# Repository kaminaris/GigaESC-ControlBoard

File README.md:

# GigaControl

Compact six-layer control card for modular GigaESC motor controllers. The MCU, CAN transceiver, IMU and signal conditioning live here; the MOSFET power stage and power supply are separate boards.

## Board views

## Hardware

- STM32F405RGT6 with an 8 MHz oscillator.
- SIT3051 CAN transceiver with onboard 120 Ω termination.
- LSM6DS3TR-C IMU on I²C.
- REF3033 analog supply/reference, also exported to the power board.
- Three 1 mm pitch 2×10 female sockets for power, PWM, feedback and external interfaces.
- USB data, SWD, Hall inputs, motor temperature, SERVO, UART and shared SPI/ADC signals pass through the power board.

Open `GigaControl.kicad_pro` in KiCad 10. Local symbols and footprints are included. Keep `HDR-TH_20P-P1.00-V-F-R2-C10-S1.00.step` beside the project for the connector models. Some other models still use `KICAD9_3DMODEL_DIR`; configure that variable if they are missing in KiCad 10.

See [connector pinout](CONNECTOR_PINOUT.md) for the current interface and [firmware adaptation guide](bldc-config/VESC-CONFIG-GUIDE.md) for the supplied VESC configuration template.

## Design notes

- 1 µF VCAP capacitors, the shared SPI/ADC filtering and the REF3033 arrangement are intentional choices reported tested by the designer. This does not imply validation of every optional interface mode.
- Bridge JP1 only when U3 (REF3033) is not fitted; it supplies VDDA from the main 3.3 V rail.
- Phase numbering is local to each board. The current GigaDFN56 pairing exchanges phase groups 1 and 3 consistently across PWM and feedback; phase 2 is unchanged.
- Adapt the firmware configuration to the actual power board and application before use.

## Repository housekeeping

Keep the KiCad project, active schematic sheets (`MCU`, `Filters`, `CAN`, `IMU`), local libraries, library tables, connector STEP model and firmware configuration sources.

Cleanup candidates, not deleted:

- Regenerable/local files: `fp-info-cache`, `GigaControl.dsn`, `GigaControl.step`, `.idea/`, `*.kicad_prl`, and `_autosave-*`.
- Old recovery files: `X3.0CH-Library.bak` and `GigaControl-backups/`, once their contents are no longer needed. Leave active lock files alone while KiCad is open.
- Unreferenced schematic files: `Connectors.kicad_sch`, `ESP32.kicad_sch`, and the empty `Power.kicad_sch`. Archive or remove after confirming they are not wanted as design references.
- Legacy footprints: `X3.0CH-Master`, `X3.0CH`, and `SolderJumper-3-0.5-Small` are not used by the current board; retain if other projects share this library.
- `production/` contains generated outputs; preserve any release/manufacturing records that still matter.

Review on 2026-09-22: saved-board DRC reports no violations, unconnected items or schematic mismatches. ERC has one warning for PB2 tied to GND. These checks do not replace hardware validation.

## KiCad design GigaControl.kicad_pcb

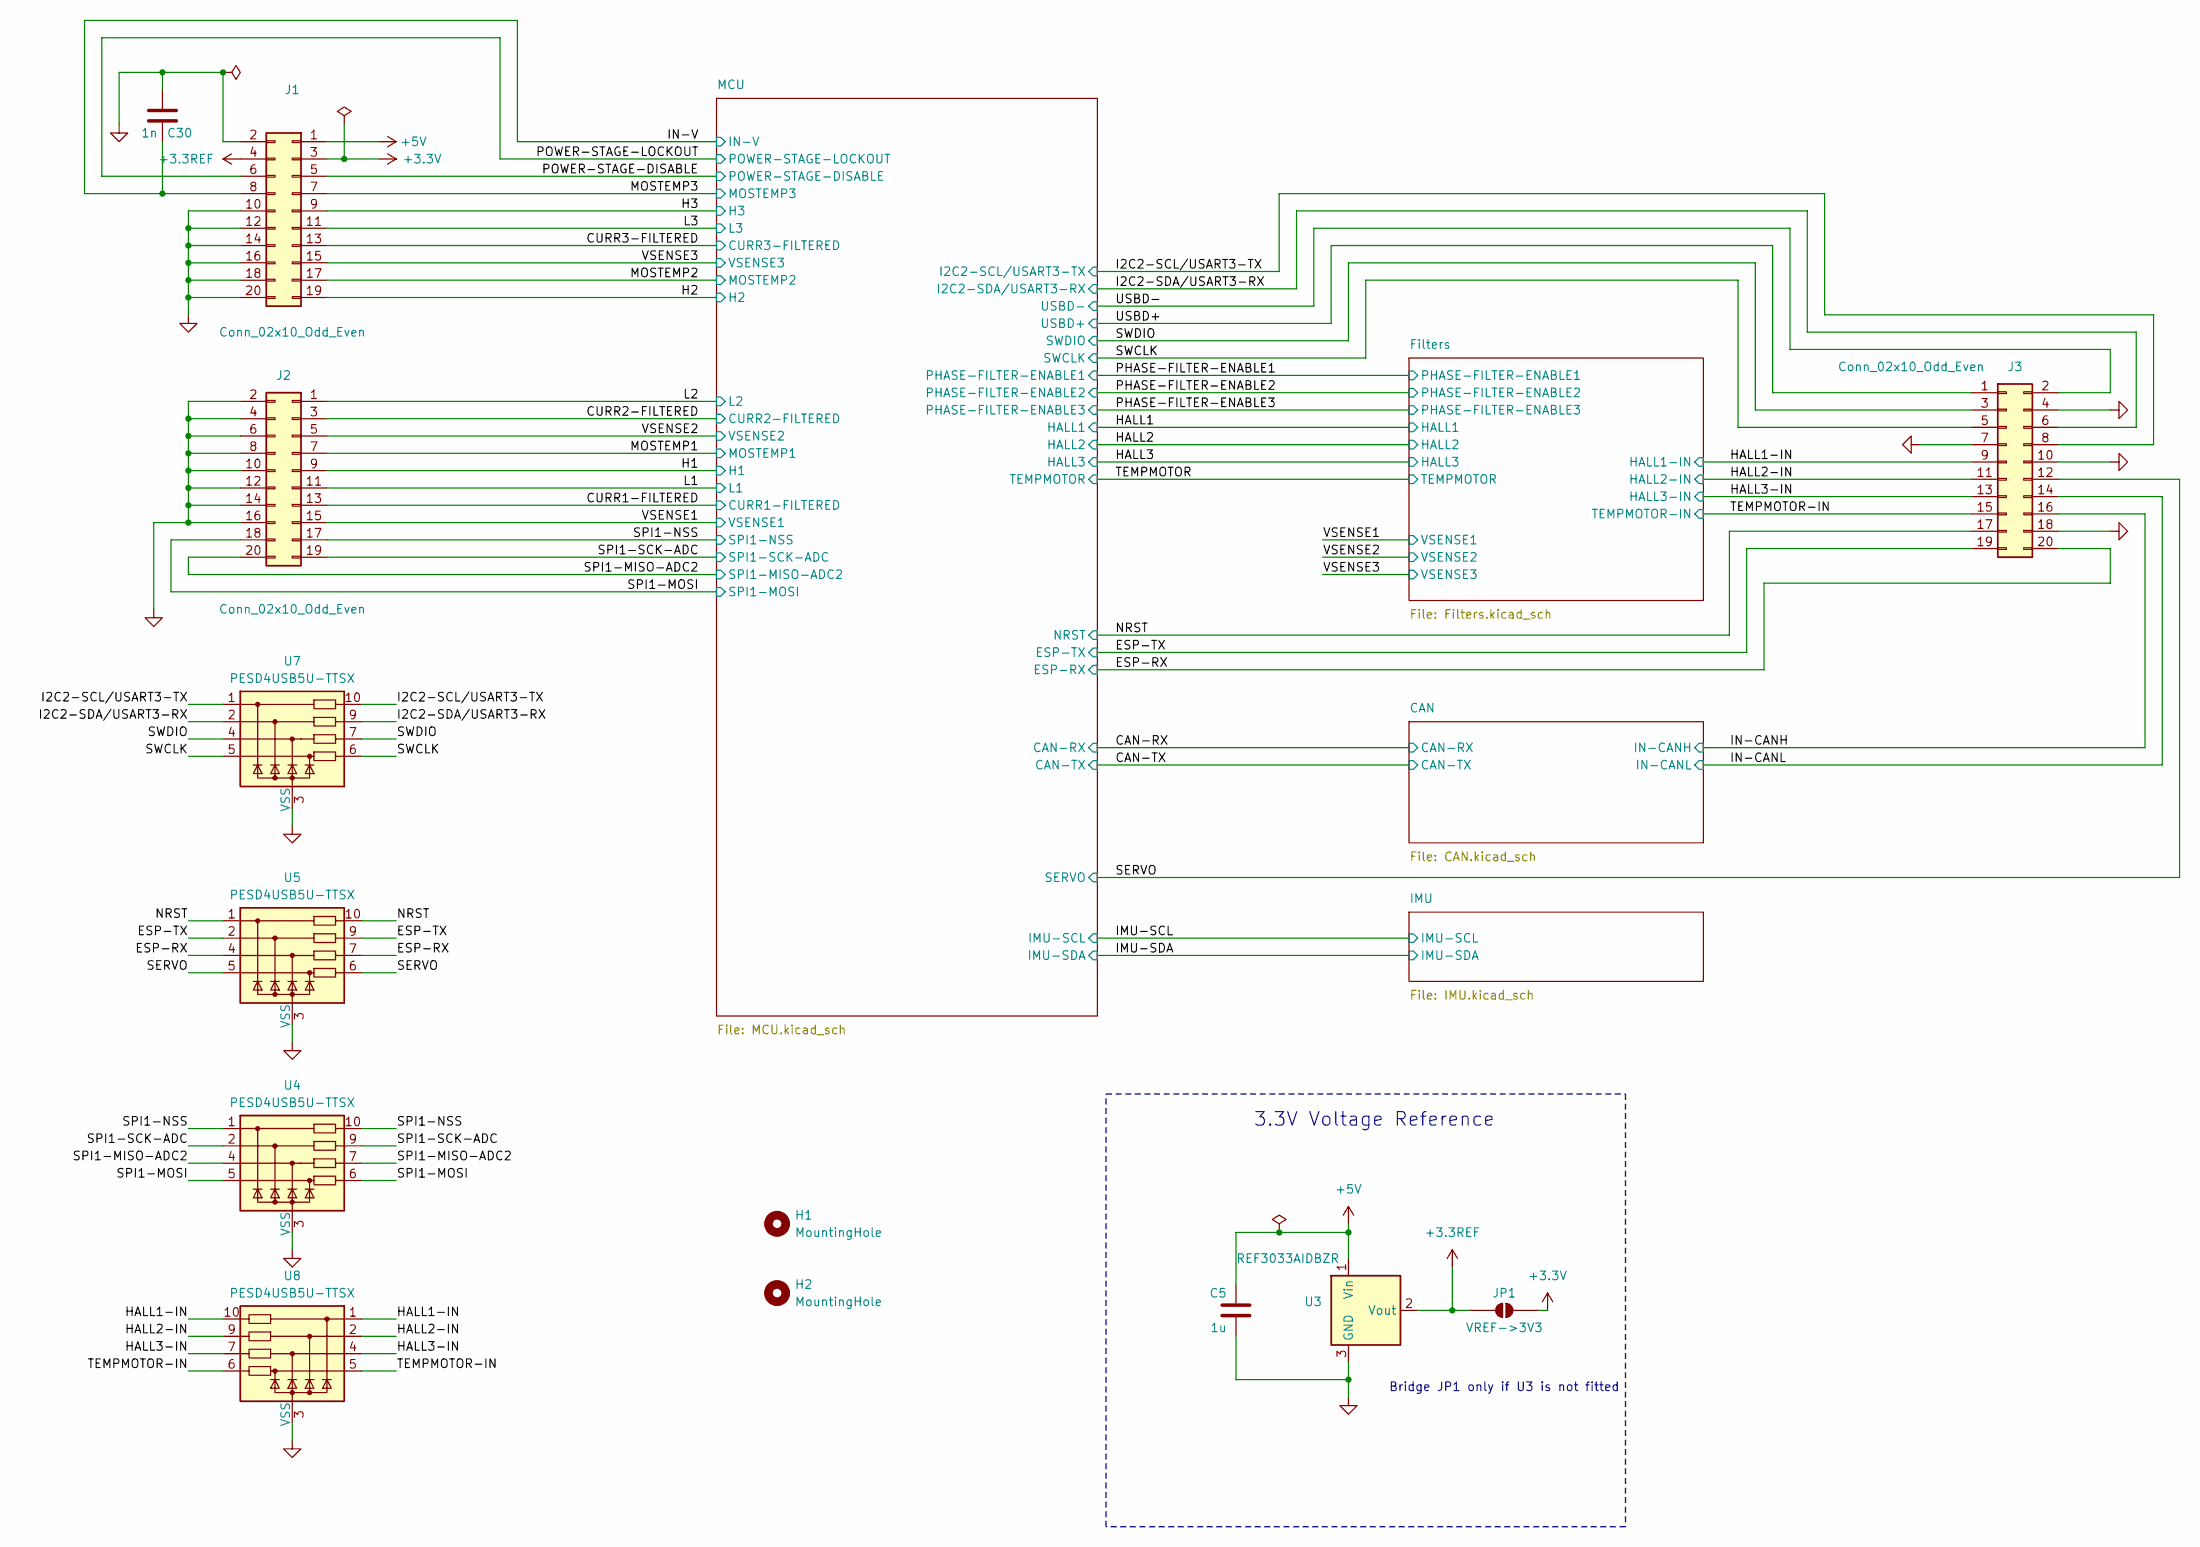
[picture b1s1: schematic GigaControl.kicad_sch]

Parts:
C5: 1u; C_0402_1005Metric; MPN C52923
C30: 1n; C_0402_1005Metric; MPN C1523
H1, H2: MountingHole; MountingHole_3.2mm_M3_DIN965
J1, J2, J3: Conn_02x10_Odd_Even; Hanxia_HX_PM1.0-2x10P_ZC; MPN HX PM1.0-2x10P ZC; LCSC C22465702
JP1: VREF->3V3; SolderJumper-2_P1.3mm_Open_RoundedPad1.0x1.5mm
U3: REF3033AIDBZR; SOT-23; MPN C36658; JLCRotOffset 0
U4, U5, U7, U8: PESD4USB5U-TTSX; Diodes_UDFN-10_1x2.5mm_P0.5mm

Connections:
+3.3REF: J1.4, JP1.1 (A), U3.2 (Vout); also elsewhere on the board
+3.3V: J1.3, JP1.2 (B); also elsewhere on the board
+5V: C5.1, J1.1, U3.1 (Vin)
/CURR1-FILTERED: J2.13; also elsewhere on the board
/CURR2-FILTERED: J2.3; also elsewhere on the board
/CURR3-FILTERED: J1.13; also elsewhere on the board
/ESP-RX: J3.20, U5.4, U5.7; also elsewhere on the board
/ESP-TX: J3.19, U5.2, U5.9; also elsewhere on the board
/H1: J2.9; also elsewhere on the board
/H2: J1.19; also elsewhere on the board
/H3: J1.9; also elsewhere on the board
/HALL1-IN: J3.9, U8.1, U8.10; also elsewhere on the board
/HALL2-IN: J3.11, U8.2, U8.9; also elsewhere on the board
/HALL3-IN: J3.13, U8.4, U8.7; also elsewhere on the board
/I2C2-SCL/USART3-TX: J3.8, U7.1, U7.10; also elsewhere on the board
/I2C2-SDA/USART3-RX: J3.6, U7.2, U7.9; also elsewhere on the board
/IN-CANH: J3.16; also elsewhere on the board
/IN-CANL: J3.14; also elsewhere on the board
/IN-V: C30.1, J1.8; also elsewhere on the board
/L1: J2.11; also elsewhere on the board
/L2: J2.1; also elsewhere on the board
/L3: J1.11; also elsewhere on the board
/MOSTEMP1: J2.7; also elsewhere on the board
/MOSTEMP2: J1.17; also elsewhere on the board
/MOSTEMP3: J1.7; also elsewhere on the board
/NRST: J3.17, U5.1, U5.10; also elsewhere on the board
/POWER-STAGE-DISABLE: J1.5; also elsewhere on the board
/POWER-STAGE-LOCKOUT: J1.6; also elsewhere on the board
/SERVO: J3.12, U5.5, U5.6; also elsewhere on the board
/SPI1-MISO-ADC2: J2.20, U4.4, U4.7; also elsewhere on the board
/SPI1-MOSI: J2.18, U4.5, U4.6; also elsewhere on the board
/SPI1-NSS: J2.17, U4.1, U4.10; also elsewhere on the board
/SPI1-SCK-ADC: J2.19, U4.2, U4.9; also elsewhere on the board
/SWCLK: J3.5, U7.5, U7.6; also elsewhere on the board
/SWDIO: J3.3, U7.4, U7.7; also elsewhere on the board
/TEMPMOTOR-IN: J3.15, U8.5, U8.6; also elsewhere on the board
/USBD+: J3.1; also elsewhere on the board
/USBD-: J3.2; also elsewhere on the board
/VSENSE1: J2.15; also elsewhere on the board
/VSENSE2: J2.5; also elsewhere on the board
/VSENSE3: J1.15; also elsewhere on the board
GND: C5.2, C30.2, J1.2, J1.10, J1.12, J1.14, J1.16, J1.18, J1.20, J2.2, J2.4, J2.6, J2.8, J2.10, J2.12, J2.14, J2.16, J3.4, J3.7, J3.10, J3.18, U3.3 (GND), U4.3 (VSS), U4.8 (VSS), U5.3 (VSS), U5.8 (VSS), U7.3 (VSS), U7.8 (VSS), U8.3 (VSS), U8.8 (VSS); also elsewhere on the board

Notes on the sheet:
3.3V Voltage Reference
Bridge JP1 only if U3 is not fitted

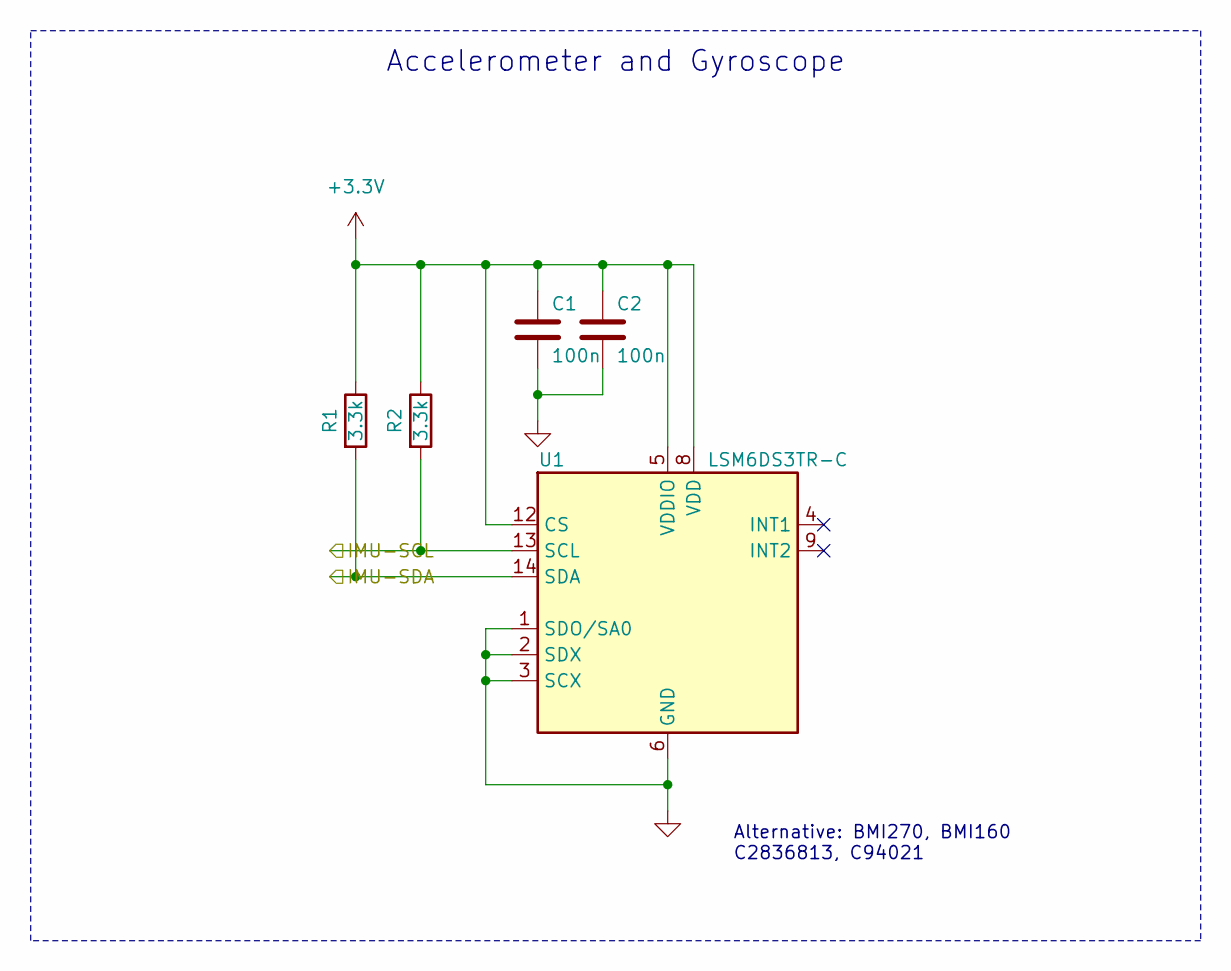
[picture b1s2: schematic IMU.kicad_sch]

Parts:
C1, C2: 100n; C_0402_1005Metric; MPN C1525
R1, R2: 3.3k; R_0402_1005Metric; MPN C25890
U1: LSM6DS3TR-C; LGA-14_3x2.5mm_P0.5mm; MPN C967633; JLCRotOffset -90

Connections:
+3.3V: C1.1, C2.1, R1.1, R2.1, U1.5 (VDDIO), U1.8 (VDD), U1.12 (CS); also elsewhere on the board
/IMU-SCL: R2.2, U1.13 (SCL); also elsewhere on the board
/IMU-SDA: R1.2, U1.14 (SDA); also elsewhere on the board
GND: C1.2, C2.2, U1.1 (SDO/SA0), U1.2 (SDX), U1.3 (SCX), U1.6 (GND), U1.7 (GND); also elsewhere on the board

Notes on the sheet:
Alternative: BMI270, BMI160 C2836813, C94021
Accelerometer and Gyroscope

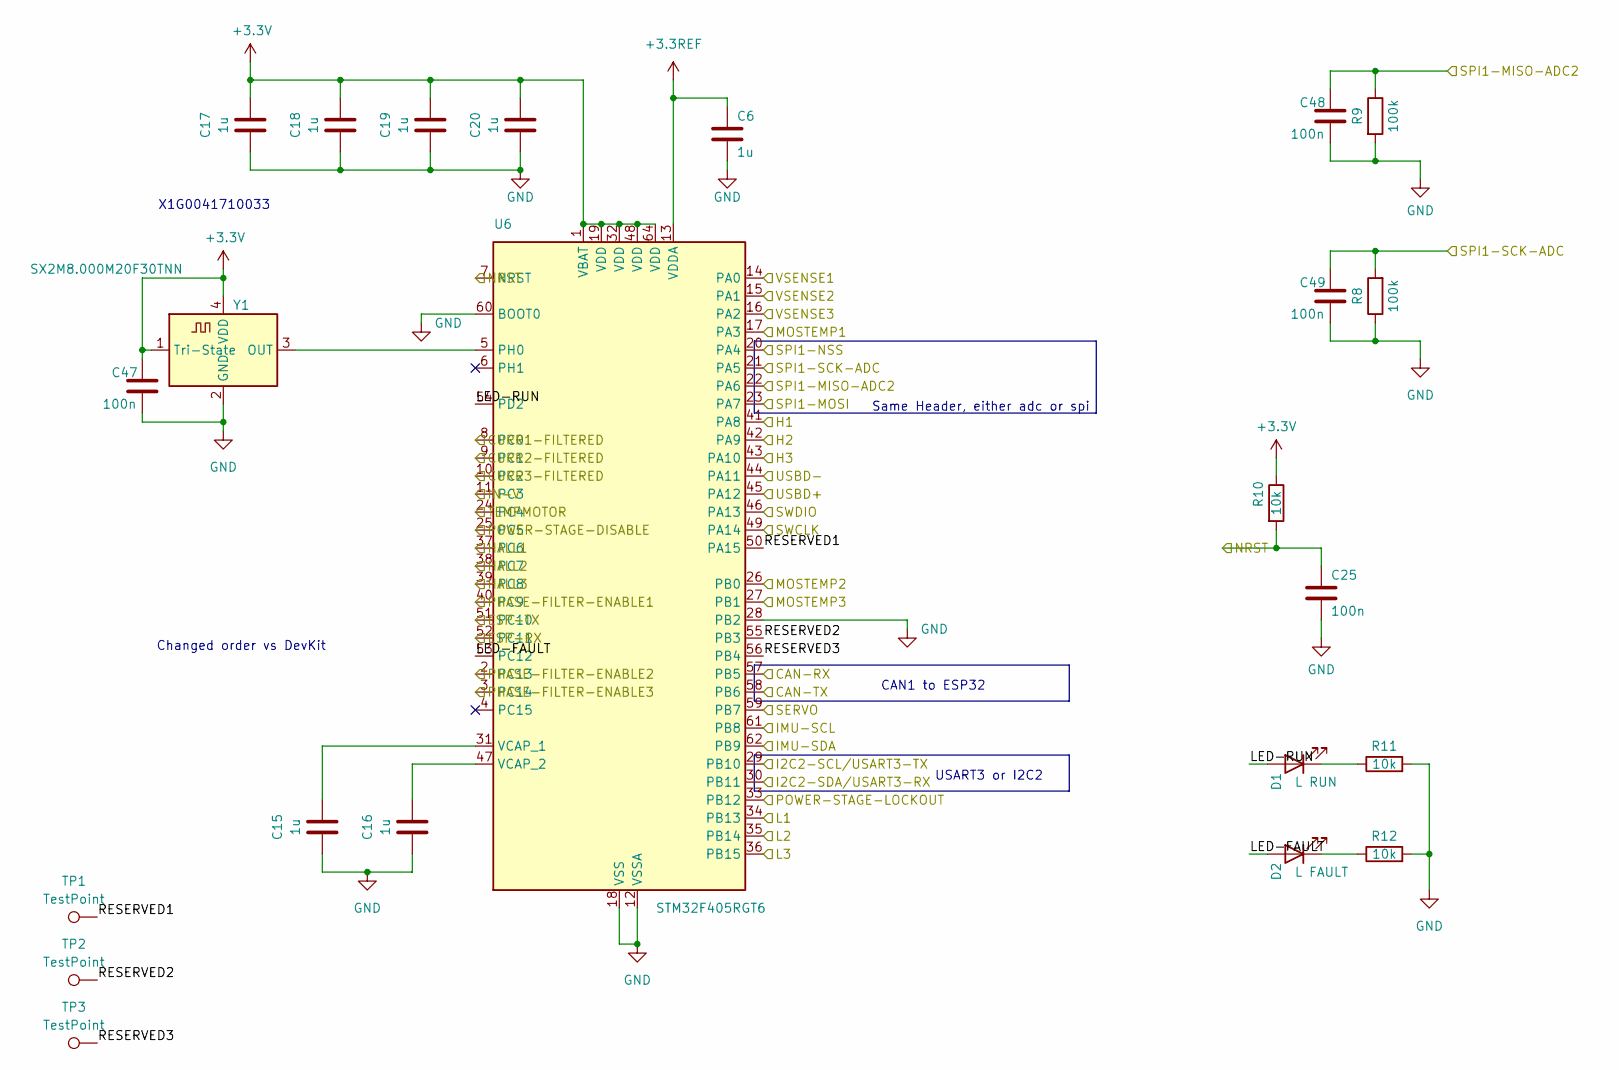
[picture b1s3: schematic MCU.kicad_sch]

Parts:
C6, C15, C16, C17, C18, C19, C20: 1u; C_0402_1005Metric; MPN C52923
C25, C47, C48, C49: 100n; C_0402_1005Metric; MPN C1525
D1: L RUN; LED_0603_1608Metric; MPN C2290
D2: L FAULT; LED_0603_1608Metric; MPN C2286
R8, R9: 100k; R_0402_1005Metric; MPN C25741
R10, R11, R12: 10k; R_0402_1005Metric; MPN C25744
TP1, TP2, TP3: TestPoint; TestPoint_Pad_D1.0mm
U6: STM32F405RGT6; LQFP-64_10x10mm_P0.5mm; MPN C15742
Y1: SX2M8.000M20F30TNN; Oscillator_SMD_ECS_2520MV-xxx-xx-4Pin_2.5x2.0mm; MPN C2901594

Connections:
+3.3REF: C6.1, U6.13 (VDDA); also elsewhere on the board
+3.3V: C17.1, C18.1, C19.1, C20.1, C47.1, R10.1, U6.1 (VBAT), U6.19 (VDD), U6.32 (VDD), U6.48 (VDD), U6.64 (VDD), Y1.1 (Tri-State), Y1.4 (VDD); also elsewhere on the board
/CAN-RX: U6.57 (PB5); also elsewhere on the board
/CAN-TX: U6.58 (PB6); also elsewhere on the board
/CURR1-FILTERED: U6.8 (PC0); also elsewhere on the board
/CURR2-FILTERED: U6.9 (PC1); also elsewhere on the board
/CURR3-FILTERED: U6.10 (PC2); also elsewhere on the board
/ESP-RX: U6.52 (PC11); also elsewhere on the board
/ESP-TX: U6.51 (PC10); also elsewhere on the board
/H1: U6.41 (PA8); also elsewhere on the board
/H2: U6.42 (PA9); also elsewhere on the board
/H3: U6.43 (PA10); also elsewhere on the board
/HALL1: U6.37 (PC6); also elsewhere on the board
/HALL2: U6.38 (PC7); also elsewhere on the board
/HALL3: U6.39 (PC8); also elsewhere on the board
/I2C2-SCL/USART3-TX: U6.29 (PB10); also elsewhere on the board
/I2C2-SDA/USART3-RX: U6.30 (PB11); also elsewhere on the board
/IMU-SCL: U6.61 (PB8); also elsewhere on the board
/IMU-SDA: U6.62 (PB9); also elsewhere on the board
/IN-V: U6.11 (PC3); also elsewhere on the board
/L1: U6.34 (PB13); also elsewhere on the board
/L2: U6.35 (PB14); also elsewhere on the board
/L3: U6.36 (PB15); also elsewhere on the board
/MCU/LED-FAULT: D2.2 (A), U6.53 (PC12)
/MCU/LED-RUN: D1.2 (A), U6.54 (PD2)
/MCU/RESERVED1: TP1.1 (1_1), U6.50 (PA15)
/MCU/RESERVED2: TP2.1 (1_1), U6.55 (PB3)
/MCU/RESERVED3: TP3.1 (1_1), U6.56 (PB4)
/MOSTEMP1: U6.17 (PA3); also elsewhere on the board
/MOSTEMP2: U6.26 (PB0); also elsewhere on the board
/MOSTEMP3: U6.27 (PB1); also elsewhere on the board
/NRST: C25.1, R10.2, U6.7 (NRST); also elsewhere on the board
/PHASE-FILTER-ENABLE1: U6.40 (PC9); also elsewhere on the board
/PHASE-FILTER-ENABLE2: U6.2 (PC13); also elsewhere on the board
/PHASE-FILTER-ENABLE3: U6.3 (PC14); also elsewhere on the board
/POWER-STAGE-DISABLE: U6.25 (PC5); also elsewhere on the board
/POWER-STAGE-LOCKOUT: U6.33 (PB12); also elsewhere on the board
/SERVO: U6.59 (PB7); also elsewhere on the board
/SPI1-MISO-ADC2: C48.1, R9.1, U6.22 (PA6); also elsewhere on the board
/SPI1-MOSI: U6.23 (PA7); also elsewhere on the board
/SPI1-NSS: U6.20 (PA4); also elsewhere on the board
/SPI1-SCK-ADC: C49.1, R8.2, U6.21 (PA5); also elsewhere on the board
/SWCLK: U6.49 (PA14); also elsewhere on the board
/SWDIO: U6.46 (PA13); also elsewhere on the board
/TEMPMOTOR: U6.24 (PC4); also elsewhere on the board
/USBD+: U6.45 (PA12); also elsewhere on the board
/USBD-: U6.44 (PA11); also elsewhere on the board
/VSENSE1: U6.14 (PA0); also elsewhere on the board
/VSENSE2: U6.15 (PA1); also elsewhere on the board
/VSENSE3: U6.16 (PA2); also elsewhere on the board
GND: C6.2, C15.2, C16.2, C17.2, C18.2, C19.2, C20.2, C25.2, C47.2, C48.2, C49.2, R8.1, R9.2, R11.2, R12.2, U6.12 (VSSA), U6.18 (VSS), U6.28 (PB2), U6.60 (BOOT0), U6.63 (VSS), Y1.2 (GND); also elsewhere on the board
unnamed: D1.1 (K), R11.1
unnamed: D2.1 (K), R12.1
unnamed: U6.5 (PH0), Y1.3 (OUT)
unnamed: C15.1, U6.31 (VCAP_1)
unnamed: C16.1, U6.47 (VCAP_2)

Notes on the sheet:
CAN1 to ESP32
USART3 or I2C2
Changed order vs DevKit
X1G0041710033
Same Header, either adc or spi

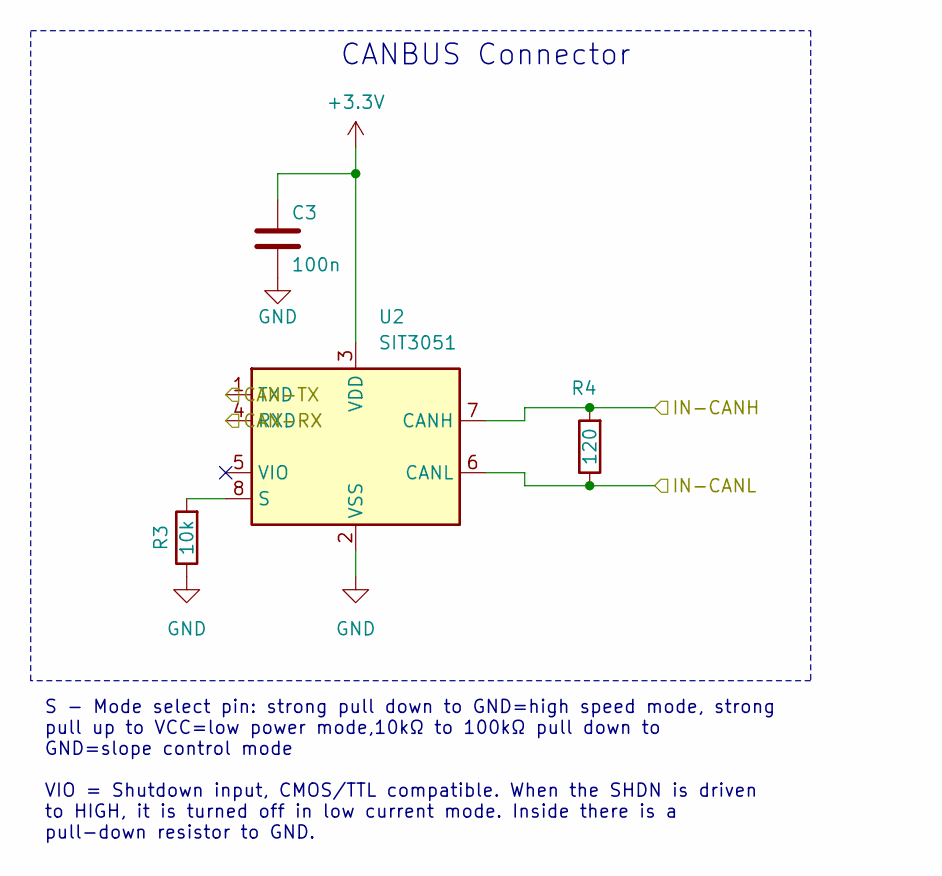
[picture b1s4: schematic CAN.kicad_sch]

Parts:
C3: 100n; C_0402_1005Metric; MPN C1525
R3: 10k; R_0402_1005Metric; MPN C25744
R4: 120; R_0402_1005Metric; MPN C25079
U2: SIT3051; DFN-8-1EP_3x3mm_P0.65mm_EP1.55x2.4mm; MPN C601078

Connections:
+3.3V: C3.1, U2.3 (VDD); also elsewhere on the board
/CAN-RX: U2.4 (RXD); also elsewhere on the board
/CAN-TX: U2.1 (TXD); also elsewhere on the board
/IN-CANH: R4.2, U2.7 (CANH); also elsewhere on the board
/IN-CANL: R4.1, U2.6 (CANL); also elsewhere on the board
GND: C3.2, R3.1, U2.2 (VSS), U2.9 (VSS); also elsewhere on the board
unnamed: R3.2, U2.8 (S)

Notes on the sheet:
CANBUS Connector
S - Mode select pin: strong pull down to GND=high speed mode, strong pull up to VCC=low power mode,10kΩ to 100kΩ pull down to GND=slope control mode VIO = Shutdown input, CMOS/TTL compatible. When the SHDN is driven to HIGH, it is turned off in low current mode. Inside there is a pull-down resistor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

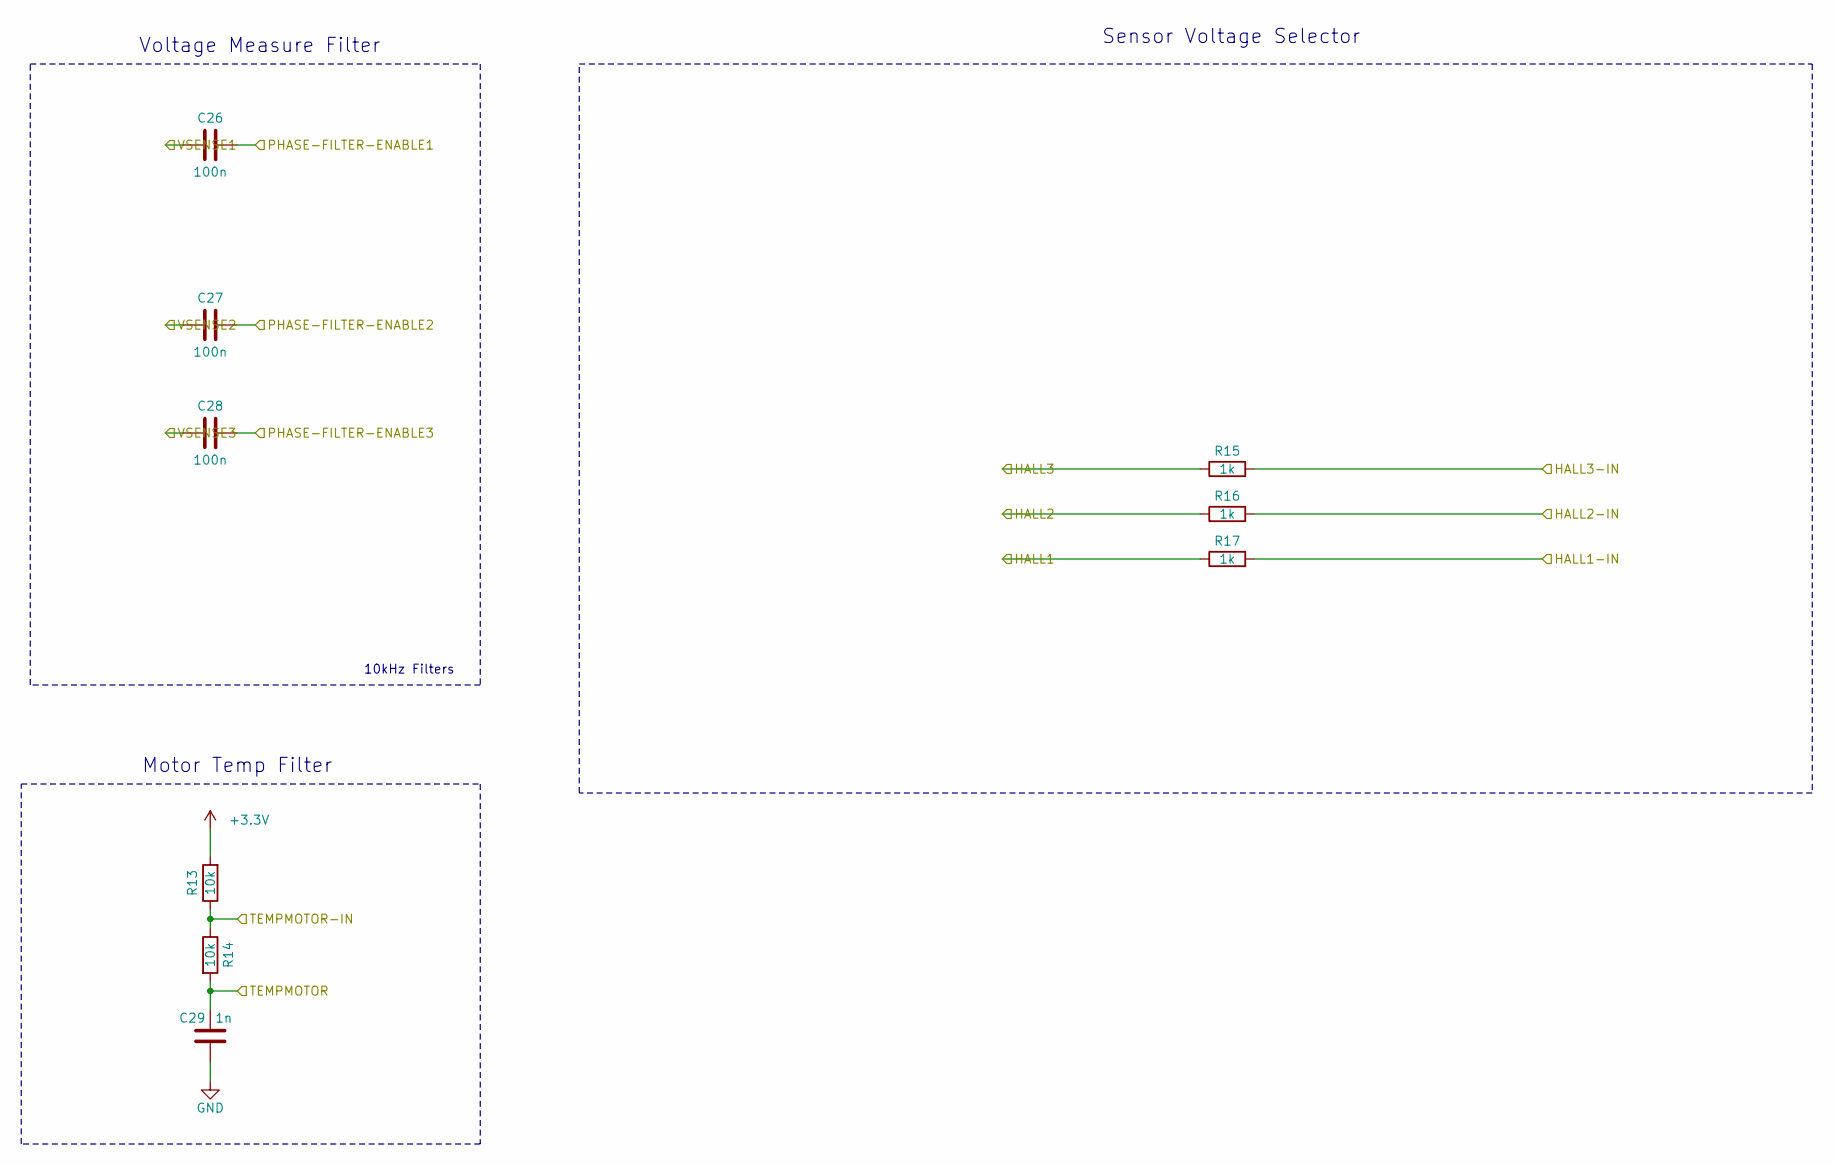
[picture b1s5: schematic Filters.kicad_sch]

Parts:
C26, C27, C28: 100n; C_0402_1005Metric; MPN C1525
C29: 1n; C_0402_1005Metric; MPN C1523
R13, R14: 10k; R_0402_1005Metric; MPN C25744
R15, R16, R17: 1k; R_0402_1005Metric; MPN C11702

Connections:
+3.3V: R13.2; also elsewhere on the board
/HALL1: R17.1; also elsewhere on the board
/HALL1-IN: R17.2; also elsewhere on the board
/HALL2: R16.1; also elsewhere on the board
/HALL2-IN: R16.2; also elsewhere on the board
/HALL3: R15.1; also elsewhere on the board
/HALL3-IN: R15.2; also elsewhere on the board
/PHASE-FILTER-ENABLE1: C26.2; also elsewhere on the board
/PHASE-FILTER-ENABLE2: C27.2; also elsewhere on the board
/PHASE-FILTER-ENABLE3: C28.2; also elsewhere on the board
/TEMPMOTOR: C29.1, R14.2; also elsewhere on the board
/TEMPMOTOR-IN: R13.1, R14.1; also elsewhere on the board
/VSENSE1: C26.1; also elsewhere on the board
/VSENSE2: C27.1; also elsewhere on the board
/VSENSE3: C28.1; also elsewhere on the board
GND: C29.2; also elsewhere on the board

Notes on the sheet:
10kHz Filters
Sensor Voltage Selector
Motor Temp Filter
Voltage Measure Filter

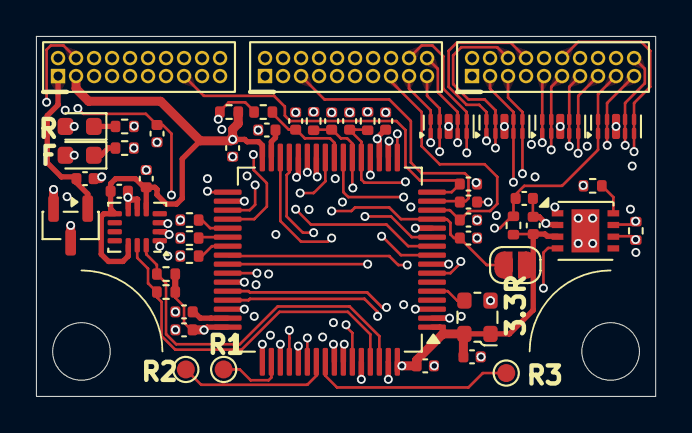
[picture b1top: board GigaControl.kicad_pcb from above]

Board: 6 copper layers, 34.4 x 20.0 mm, 54 parts (0 on the bottom side), 64 nets.
